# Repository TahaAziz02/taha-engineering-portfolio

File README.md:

# Taha Aziz - Engineering Portfolio

Electrical Engineer focused on embedded systems, robotics, controls, industrial automation, and product development.

## Featured Projects

### Reconstructed Audi Speaker Bracket 
Designed and manufactured a custom speaker mounting bracket for a 2012 Audi A7 using CAD and additive manufacturing techniques. Reverse-engineered mounting geometry, verified fitment constraints, and accounted for structural loading, vibration, and installation requirements to enable aftermarket speaker integration.

### Smart Space Management System
Computer vision and sensor-based monitoring system for tracking facility usage.

### FSAE Battery Thermistor Board
PCB design project for monitoring battery cell temperatures using NTC thermistors and Orion BMS integration.

### Smart CNC Spindle Cooling System

Arduino Nano-based water cooling controller for a CNC machine spindle. Through operational observation, the system improved CNC machine uptime by approximately 40% by reducing cooling-related interruptions and manual pump monitoring.

### Embedded Telemetry Computer
Long-term embedded systems project focused on IMU sensing, telemetry, SD logging, watchdog logic, and fault handling.

## Contact

LinkedIn: https://www.linkedin.com/in/aziz-taha/ 
Email:  mtaziz1@ualberta.ca
Phone: 780-974-8254

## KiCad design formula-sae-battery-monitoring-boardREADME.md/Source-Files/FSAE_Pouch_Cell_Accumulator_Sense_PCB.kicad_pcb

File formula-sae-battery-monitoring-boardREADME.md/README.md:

# Formula SAE EV In-Segment Battery Monitoring Board

## Overview

Contributed to the design and development of a battery temperature monitoring system for the University of Alberta Formula SAE Electric Vehicle team. The project focused on designing a reliable thermistor interface board for the Orion Battery Management System (BMS), enabling accurate temperature monitoring of pouch-cell battery modules while meeting Formula SAE EV safety requirements.

---

## Problem

Formula SAE Electric vehicles require continuous battery temperature monitoring to ensure safe operation and compliance with competition regulations. The monitoring system needed to provide reliable sensor connectivity, simplify assembly and servicing, and integrate directly with the Orion BMS.

---

## My Contributions

My responsibilities included:

- Schematic capture in KiCad
- PCB layout and routing
- Thermistor placement planning
- Connector selection
- Orion BMS integration
- Design reviews
- Rule compliance verification
- Collaboration with mechanical and controls teams

---

## Hardware

- Orion Battery Management System (BMS)
- NTC Thermistors
- Custom KiCad PCB
- JST Connectors
- Samtec Board Connectors

---

## Design Considerations

The PCB was designed with emphasis on:

- Accurate temperature sensing
- Reliable electrical connections
- Ease of manufacturing
- Ease of serviceability
- Electrical isolation
- Battery module packaging constraints
- Formula SAE EV rule compliance

---

## Engineering Challenges

### Thermistor Interface Architecture

Previous accumulator designs used thermistors connected in series due to the battery modules utilizing thermal diodes rather than true NTC thermistors. The redesigned system instead routes each thermistor independently to the connector, allowing every sensor to be monitored individually by the BMS.

This architecture required routing 54 dedicated thermistor signal lines while maintaining a compact PCB footprint and organized connector layout.

---

### Redundant Voltage Measurement

The accumulator was designed to support redundant voltage sensing for each battery cell.

Each cell includes three independent voltage taps with separate fusing to provide fault tolerance for the battery management system. This architecture allows the system to continue operating even if individual voltage taps or fuses fail.

Connector placement was optimized so that each cell tap was located adjacent to its corresponding busbar, reducing wiring complexity while simplifying assembly and maintenance.

---

### Mechanical Integration

The PCB had to fit completely within the battery module while avoiding interference with:

- Cell compression hardware
- Busbars
- High-voltage connections
- Battery tabs
- Service access

Connector locations were selected to minimize harness length while maintaining accessibility during assembly and maintenance.

---

### Electrical Safety

The board was designed to interface directly with the Orion BMS using electrically isolated 10kΩ NTC thermistors with a common β value of 3380 K.

**Maintaining identical thermistor characteristics and proper electrical isolation was essential for accurate temperature monitoring and safe operation.**

---

## Skills Demonstrated

- PCB Design
- KiCad
- Schematic Capture
- PCB Layout
- Battery Management Systems
- Sensor Integration
- Design Reviews
- Engineering Documentation
- Cross-Disciplinary Collaboration

---

## Outcome

Contributed to the successful development of a battery temperature monitoring solution that supported safe battery operation and integration with the vehicle's Orion BMS. The project strengthened practical experience in PCB design, battery systems, and engineering collaboration within a multidisciplinary motorsports team.

---

## Photos

### Schematic

### PCB Layout

### PCB 3D Viewer

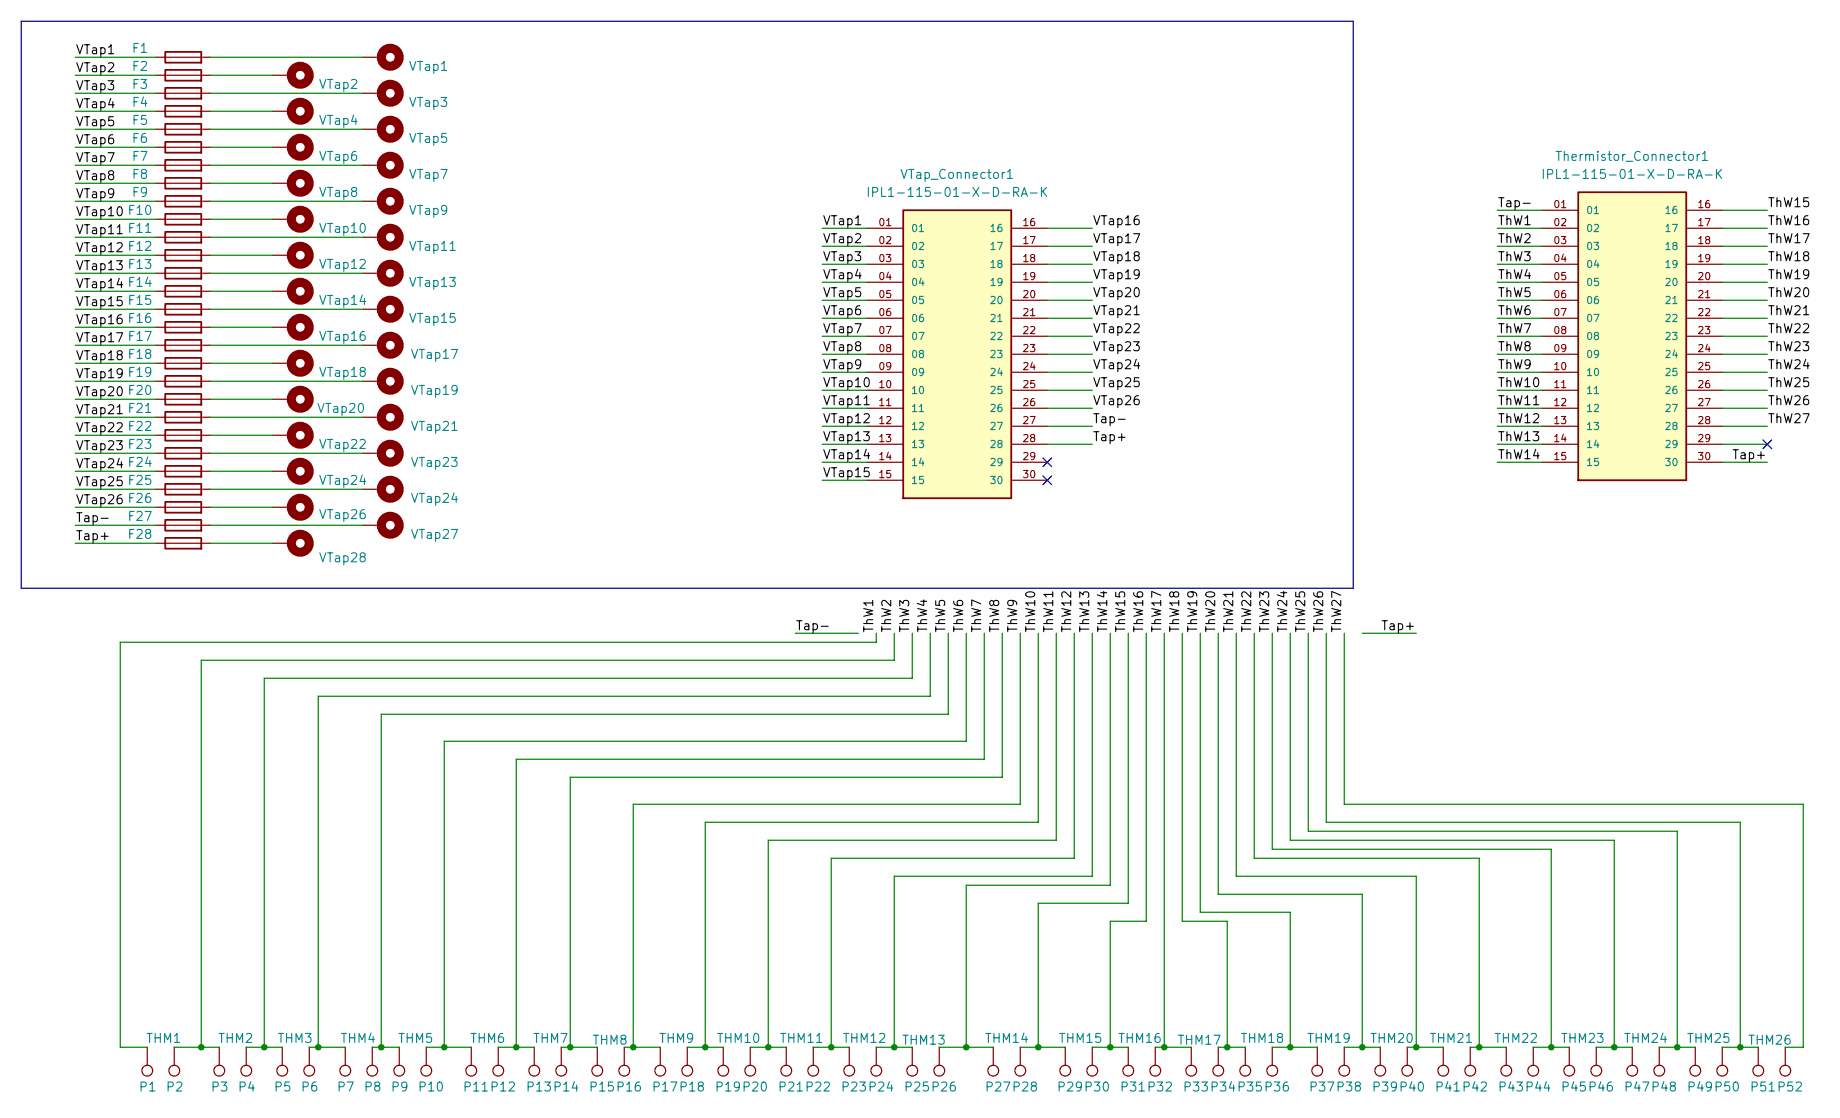
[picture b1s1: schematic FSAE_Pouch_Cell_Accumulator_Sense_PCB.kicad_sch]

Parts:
F1, F2, F3, F4, F5, F6, F7, F8, F9, F10, F11, F12, F13, F14, F15, F16, F17, F18, F19, F20, F21, F22, F23, F24, F25, F26, F27, F28: Fuse; Fuse_1206_3216Metric_Pad1.42x1.75mm_HandSolder
H1: VTap2; MountingHole_5.3mm_M5_DIN965_Pad_TopBottom
H2: VTap4; MountingHole_5.3mm_M5_DIN965_Pad_TopBottom
H3: VTap6; MountingHole_5.3mm_M5_DIN965_Pad_TopBottom
H4: VTap8; MountingHole_5.3mm_M5_DIN965_Pad_TopBottom
H5: VTap10; MountingHole_5.3mm_M5_DIN965_Pad_TopBottom
H6: VTap12; MountingHole_5.3mm_M5_DIN965_Pad_TopBottom
H7: VTap14; MountingHole_5.3mm_M5_DIN965_Pad_TopBottom
H8: VTap16; MountingHole_5.3mm_M5_DIN965_Pad_TopBottom
H9: VTap18; MountingHole_5.3mm_M5_DIN965_Pad_TopBottom
H10: VTap20; MountingHole_5.3mm_M5_DIN965_Pad_TopBottom
H11: VTap22; MountingHole_5.3mm_M5_DIN965_Pad_TopBottom
H12, H27: VTap24; MountingHole_5.3mm_M5_DIN965_Pad_TopBottom
H13: VTap26; MountingHole_5.3mm_M5_DIN965_Pad_TopBottom
H14: VTap28; MountingHole_5.3mm_M5_DIN965_Pad_TopBottom
H15: VTap1; MountingHole_5.3mm_M5_DIN965_Pad_TopBottom
H16: VTap3; MountingHole_5.3mm_M5_DIN965_Pad_TopBottom
H17: VTap5; MountingHole_5.3mm_M5_DIN965_Pad_TopBottom
H18: VTap7; MountingHole_5.3mm_M5_DIN965_Pad_TopBottom
H19: VTap9; MountingHole_5.3mm_M5_DIN965_Pad_TopBottom
H20: VTap11; MountingHole_5.3mm_M5_DIN965_Pad_TopBottom
H21: VTap13; MountingHole_5.3mm_M5_DIN965_Pad_TopBottom
H22: VTap15; MountingHole_5.3mm_M5_DIN965_Pad_TopBottom
H23: VTap17; MountingHole_5.3mm_M5_DIN965_Pad_TopBottom
H24: VTap19; MountingHole_5.3mm_M5_DIN965_Pad_TopBottom
H25: VTap21; MountingHole_5.3mm_M5_DIN965_Pad_TopBottom
H26: VTap23; MountingHole_5.3mm_M5_DIN965_Pad_TopBottom
H28: VTap27; MountingHole_5.3mm_M5_DIN965_Pad_TopBottom
P1: THM1; TestPoint_THTPad_D2.5mm_Drill1.2mm
P2, P4, P6, P8, P10, P12, P14, P16, P18, P20, P22, P24, P26, P28, P30, P32, P34, P36, P38, P40, P42, P44, P46, P48, P50, P52: Pad; TestPoint_THTPad_D2.5mm_Drill1.2mm
P3: THM2; TestPoint_THTPad_D2.5mm_Drill1.2mm
P5: THM3; TestPoint_THTPad_D2.5mm_Drill1.2mm
P7: THM4; TestPoint_THTPad_D2.5mm_Drill1.2mm
P9: THM5; TestPoint_THTPad_D2.5mm_Drill1.2mm
P11: THM6; TestPoint_THTPad_D2.5mm_Drill1.2mm
P13: THM7; TestPoint_THTPad_D2.5mm_Drill1.2mm
P15: THM8; TestPoint_THTPad_D2.5mm_Drill1.2mm
P17: THM9; TestPoint_THTPad_D2.5mm_Drill1.2mm
P19: THM10; TestPoint_THTPad_D2.5mm_Drill1.2mm
P21: THM11; TestPoint_THTPad_D2.5mm_Drill1.2mm
P23: THM12; TestPoint_THTPad_D2.5mm_Drill1.2mm
P25: THM13; TestPoint_THTPad_D2.5mm_Drill1.2mm
P27: THM14; TestPoint_THTPad_D2.5mm_Drill1.2mm
P29: THM15; TestPoint_THTPad_D2.5mm_Drill1.2mm
P31: THM16; TestPoint_THTPad_D2.5mm_Drill1.2mm
P33: THM17; TestPoint_THTPad_D2.5mm_Drill1.2mm
P35: THM18; TestPoint_THTPad_D2.5mm_Drill1.2mm
P37: THM19; TestPoint_THTPad_D2.5mm_Drill1.2mm
P39: THM20; TestPoint_THTPad_D2.5mm_Drill1.2mm
P41: THM21; TestPoint_THTPad_D2.5mm_Drill1.2mm
P43: THM22; TestPoint_THTPad_D2.5mm_Drill1.2mm
P45: THM23; TestPoint_THTPad_D2.5mm_Drill1.2mm
P47: THM24; TestPoint_THTPad_D2.5mm_Drill1.2mm
P49: THM25; TestPoint_THTPad_D2.5mm_Drill1.2mm
P51: THM26; TestPoint_THTPad_D2.5mm_Drill1.2mm
Thermistor_Connector1: IPL1-115-01-X-D-RA-K; SAMTEC_IPL1-115-01-X-D-RA-K; PARTREV E
VTap_Connector1: IPL1-115-01-X-D-RA-K; SAMTEC_IPL1-115-01-X-D-RA-K; PARTREV E

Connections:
/Tap+: F28.1, Thermistor_Connector1.30, VTap_Connector1.28
/Tap-: F27.1, Thermistor_Connector1.01, VTap_Connector1.27
/ThW1: P1.1, Thermistor_Connector1.02
/ThW2: P2.1, P3.1, Thermistor_Connector1.03
/ThW3: P4.1, P5.1, Thermistor_Connector1.04
/ThW4: P6.1, P7.1, Thermistor_Connector1.05
/ThW5: P8.1, P9.1, Thermistor_Connector1.06
/ThW6: P10.1, P11.1, Thermistor_Connector1.07
/ThW7: P12.1, P13.1, Thermistor_Connector1.08
/ThW8: P14.1, P15.1, Thermistor_Connector1.09
/ThW9: P16.1, P17.1, Thermistor_Connector1.10
/ThW10: P18.1, P19.1, Thermistor_Connector1.11
/ThW11: P20.1, P21.1, Thermistor_Connector1.12
/ThW12: P22.1, P23.1, Thermistor_Connector1.13
/ThW13: P24.1, P25.1, Thermistor_Connector1.14
/ThW14: P26.1, P27.1, Thermistor_Connector1.15
/ThW15: P28.1, P29.1, Thermistor_Connector1.16
/ThW16: P30.1, P31.1, Thermistor_Connector1.17
/ThW17: P32.1, P33.1, Thermistor_Connector1.18
/ThW18: P34.1, P35.1, Thermistor_Connector1.19
/ThW19: P36.1, P37.1, Thermistor_Connector1.20
/ThW20: P38.1, P39.1, Thermistor_Connector1.21
/ThW21: P40.1, P41.1, Thermistor_Connector1.22
/ThW22: P42.1, P43.1, Thermistor_Connector1.23
/ThW23: P44.1, P45.1, Thermistor_Connector1.24
/ThW24: P46.1, P47.1, Thermistor_Connector1.25
/ThW25: P48.1, P49.1, Thermistor_Connector1.26
/ThW26: P50.1, P51.1, Thermistor_Connector1.27
/ThW27: P52.1, Thermistor_Connector1.28
/VTap1: F1.1, VTap_Connector1.01
/VTap2: F2.1, VTap_Connector1.02
/VTap3: F3.1, VTap_Connector1.03
/VTap4: F4.1, VTap_Connector1.04
/VTap5: F5.1, VTap_Connector1.05
/VTap6: F6.1, VTap_Connector1.06
/VTap7: F7.1, VTap_Connector1.07
/VTap8: F8.1, VTap_Connector1.08
/VTap9: F9.1, VTap_Connector1.09
/VTap10: F10.1, VTap_Connector1.10
/VTap11: F11.1, VTap_Connector1.11
/VTap12: F12.1, VTap_Connector1.12
/VTap13: F13.1, VTap_Connector1.13
/VTap14: F14.1, VTap_Connector1.14
/VTap15: F15.1, VTap_Connector1.15
/VTap16: F16.1, VTap_Connector1.16
/VTap17: F17.1, VTap_Connector1.17
/VTap18: F18.1, VTap_Connector1.18
/VTap19: F19.1, VTap_Connector1.19
/VTap20: F20.1, VTap_Connector1.20
/VTap21: F21.1, VTap_Connector1.21
/VTap22: F22.1, VTap_Connector1.22
/VTap23: F23.1, VTap_Connector1.23
/VTap24: F24.1, VTap_Connector1.24
/VTap25: F25.1, VTap_Connector1.25
/VTap26: F26.1, VTap_Connector1.26
unnamed: F1.2, H15.1
unnamed: F2.2, H1.1
unnamed: F3.2, H16.1
unnamed: F4.2, H2.1
unnamed: F5.2, H17.1
unnamed: F6.2, H3.1
unnamed: F7.2, H18.1
unnamed: F8.2, H4.1
unnamed: F9.2, H19.1
unnamed: F10.2, H5.1
unnamed: F11.2, H20.1
unnamed: F12.2, H6.1
unnamed: F13.2, H21.1
unnamed: F14.2, H7.1
unnamed: F15.2, H22.1
unnamed: F16.2, H8.1
unnamed: F17.2, H23.1
unnamed: F18.2, H9.1
unnamed: F19.2, H24.1
unnamed: F20.2, H10.1
unnamed: F21.2, H25.1
unnamed: F22.2, H11.1
unnamed: F23.2, H26.1
unnamed: F24.2, H12.1
unnamed: F25.2, H27.1
unnamed: F26.2, H13.1
unnamed: F27.2, H28.1
unnamed: F28.2, H14.1

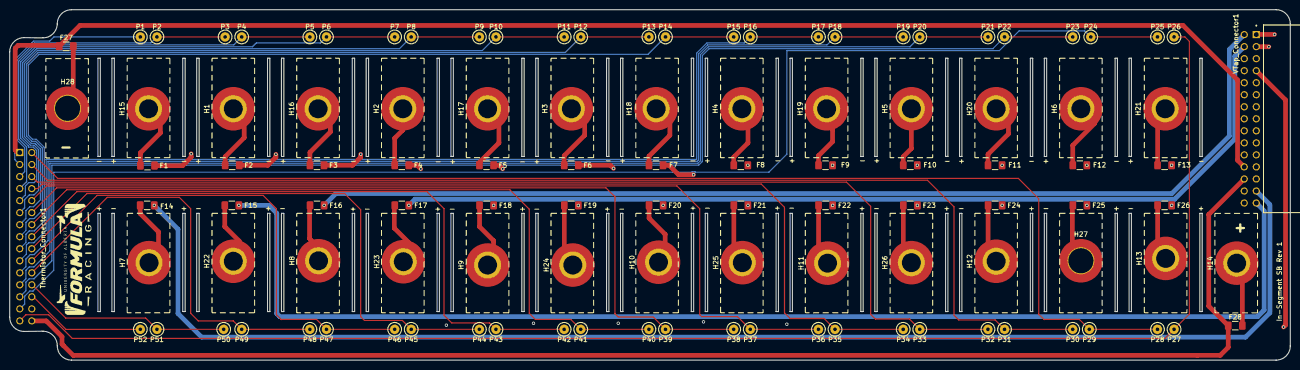
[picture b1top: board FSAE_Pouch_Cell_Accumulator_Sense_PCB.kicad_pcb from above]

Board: 4 copper layers, 270.4 x 74.0 mm, 110 parts (1 on the bottom side), 83 nets.

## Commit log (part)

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2026-06-23 Create README.md
    Overview
2026-06-23 Create README.md
    Audi A7 Speaker Bracket
2026-06-23 Create images
2026-06-23 Rename Mount Screen Shot.png to Mount CAD.png
2026-06-24 Create butterdome-occupancy-monitoring-system
2026-06-29 Rename RAPID.png to RAPiD_Algorithm_Snapshot.png
